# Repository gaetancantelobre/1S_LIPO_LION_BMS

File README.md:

# 1S LiPo/Li-ion BMS (BQ21040DBVT)

This repository contains all the design files for a single-cell (1s) Battery Management System (BMS) for Lithium-Polymer (LiPo) and Lithium-Ion (Li-ion) batteries. The core of this design is the Texas Instruments BQ21040DBVT, a highly integrated battery charger and protection IC.

**400mA output, adjustable via the R2 resistor.**

This BMS is perfect for low-power applications where you need to safely charge and protect a single lithium-based battery cell.

## Features
**Single-Cell Charging**: Safely and efficiently charges a single LiPo or Li-ion cell.

**Over-Charge Protection**: Prevents the battery from being charged beyond its safe voltage limit, extending battery life.

**Over-Discharge Protection**: Stops the battery from being discharged too low, preventing irreversible damage.

**Short-Circuit Protection**: Protects the battery and connected load from damage in the event of a short circuit.

## Repository Contents
**schematic**: Contains the circuit diagram showing the connections for the BQ21040DBVT and all other components.

**pcb**: Includes the Gerber files for the printed circuit board (PCB), ready for manufacturing.

**bom**: A complete Bill of Materials (BOM) listing all the necessary components, along with part numbers and supplier information.

Getting Started
To get started, you can use the Gerber files in the pcb/ folder to have the boards manufactured. Then, use the BOM to order the components and assemble the circuit. The schematic will be your guide during the assembly process.

Disclaimer
This design is provided as-is. While it has been created with careful consideration, it is the user's responsibility to verify its suitability for their specific application. Please refer to the datasheets for the BQ21040DBVT and other components for detailed electrical specifications and safe operating conditions.

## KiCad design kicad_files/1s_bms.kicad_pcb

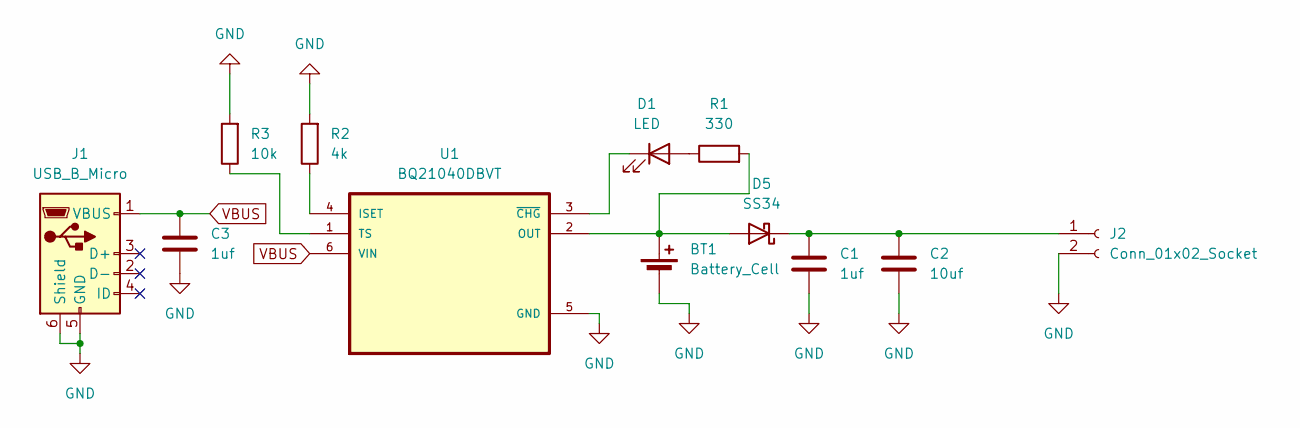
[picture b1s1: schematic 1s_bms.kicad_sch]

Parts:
BT1: Battery_Cell; PinHeader_1x02_P2.54mm_Vertical
C1, C3: 1uf; C_0603_1608Metric
C2: 10uf; C_0805_2012Metric
D1: LED; L_1206_3216Metric
D5: SS34; D_SMA
J1: USB_B_Micro; USB_Micro-B_Amphenol_10103594-0001LF_Horizontal
J2: Conn_01x02_Socket; PinHeader_1x02_P2.54mm_Vertical
R1: 330; R_0603_1608Metric
R2: 4k; R_0603_1608Metric
R3: 10k; R_0603_1608Metric
U1: BQ21040DBVT; SOT95P280X145-6N

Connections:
GND: BT1.2 (-), C1.2, C2.2, C3.2, J1.4 (ID), J1.5 (GND), J1.6 (Shield), J2.2, R2.2, R3.2, U1.5 (GND)
unnamed: BT1.1 (+), D5.2 (A), R1.2, U1.2 (OUT)
unnamed: D1.2 (A), R1.1
unnamed: D1.1 (K), U1.3 (~CHG)
unnamed: C1.1, C2.1, D5.1 (K), J2.1
unnamed: R2.1, U1.4 (ISET)
unnamed: R3.1, U1.1 (TS)
VBUS: C3.1, J1.1 (VBUS), U1.6 (VIN)

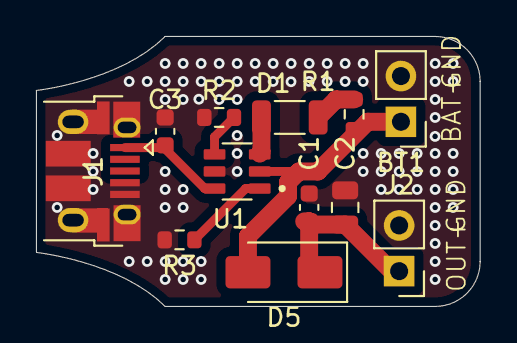
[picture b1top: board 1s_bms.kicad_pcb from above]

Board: 2 copper layers, 24.7 x 15.0 mm, 12 parts (0 on the bottom side), 8 nets.

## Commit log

2025-08-05 added the files
2025-08-05 added changes and final readme
